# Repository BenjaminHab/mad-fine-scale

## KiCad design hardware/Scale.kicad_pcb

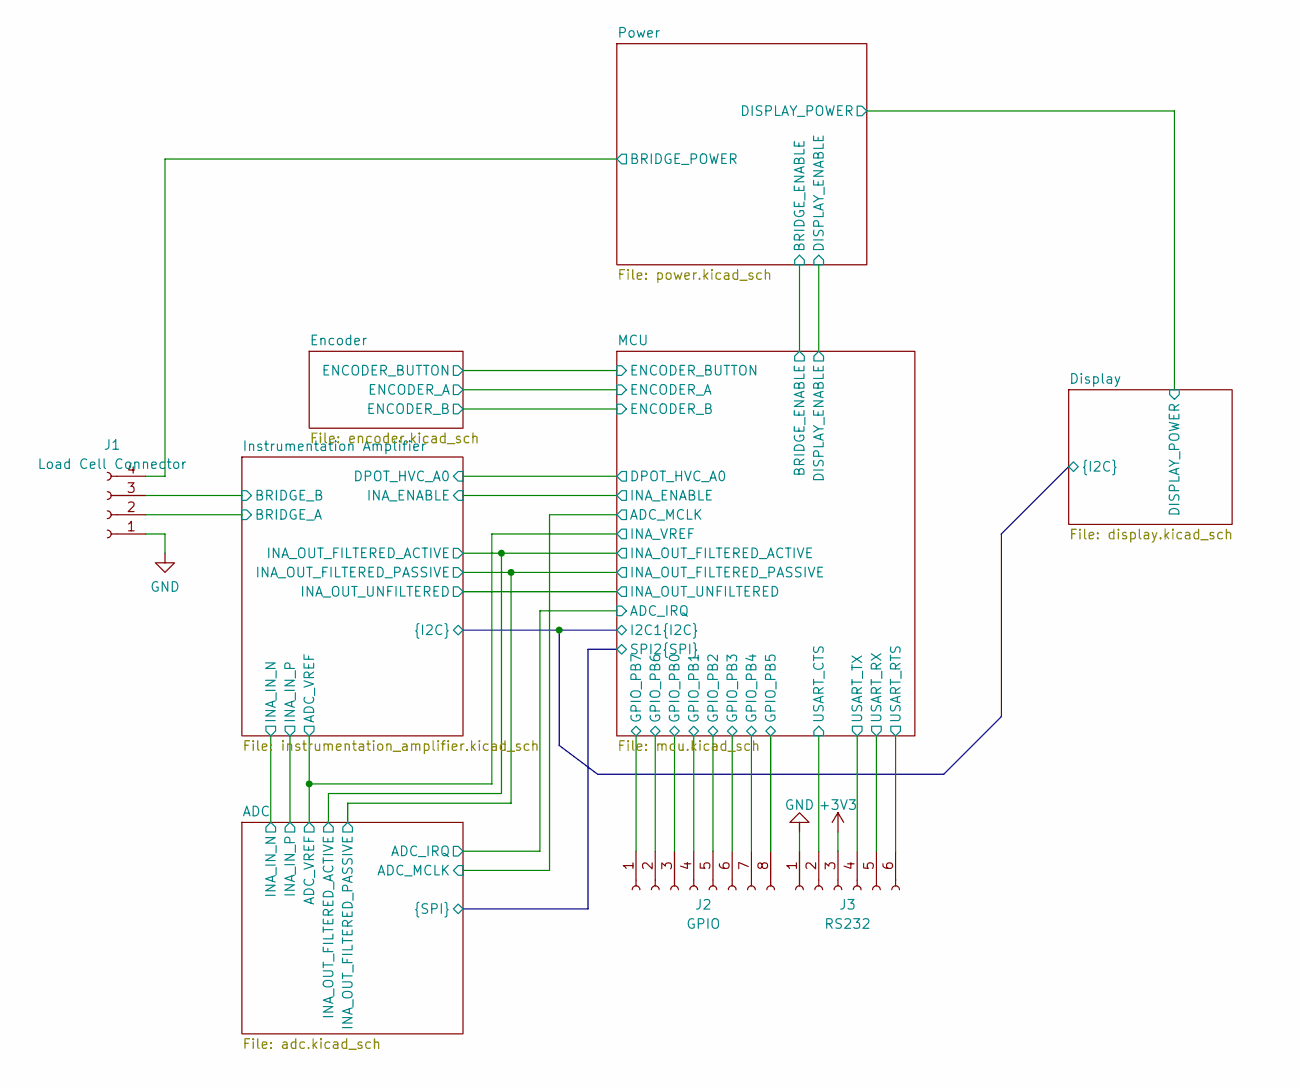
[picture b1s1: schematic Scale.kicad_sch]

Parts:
J1: Load Cell Connector; PinHeader_1x04_P2.54mm_Vertical
J2: GPIO; PinHeader_1x08_P2.54mm_Vertical
J3: RS232; PinHeader_1x06_P2.54mm_Vertical

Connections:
+3V3: J3.3; also elsewhere on the board
/Instrumentation Amplifier/BRIDGE_A: J1.2; also elsewhere on the board
/Instrumentation Amplifier/BRIDGE_B: J1.3; also elsewhere on the board
/MCU/GPIO_PB0: J2.3; also elsewhere on the board
/MCU/GPIO_PB1: J2.4; also elsewhere on the board
/MCU/GPIO_PB2: J2.5; also elsewhere on the board
/MCU/GPIO_PB3: J2.6; also elsewhere on the board
/MCU/GPIO_PB4: J2.7; also elsewhere on the board
/MCU/GPIO_PB5: J2.8; also elsewhere on the board
/MCU/GPIO_PB6: J2.2; also elsewhere on the board
/MCU/GPIO_PB7: J2.1; also elsewhere on the board
/MCU/USART_CTS: J3.2; also elsewhere on the board
/MCU/USART_RTS: J3.6; also elsewhere on the board
/MCU/USART_RX: J3.5; also elsewhere on the board
/MCU/USART_TX: J3.4; also elsewhere on the board
/Power/BRIDGE_POWER: J1.4; also elsewhere on the board
GND: J1.1, J3.1; also elsewhere on the board

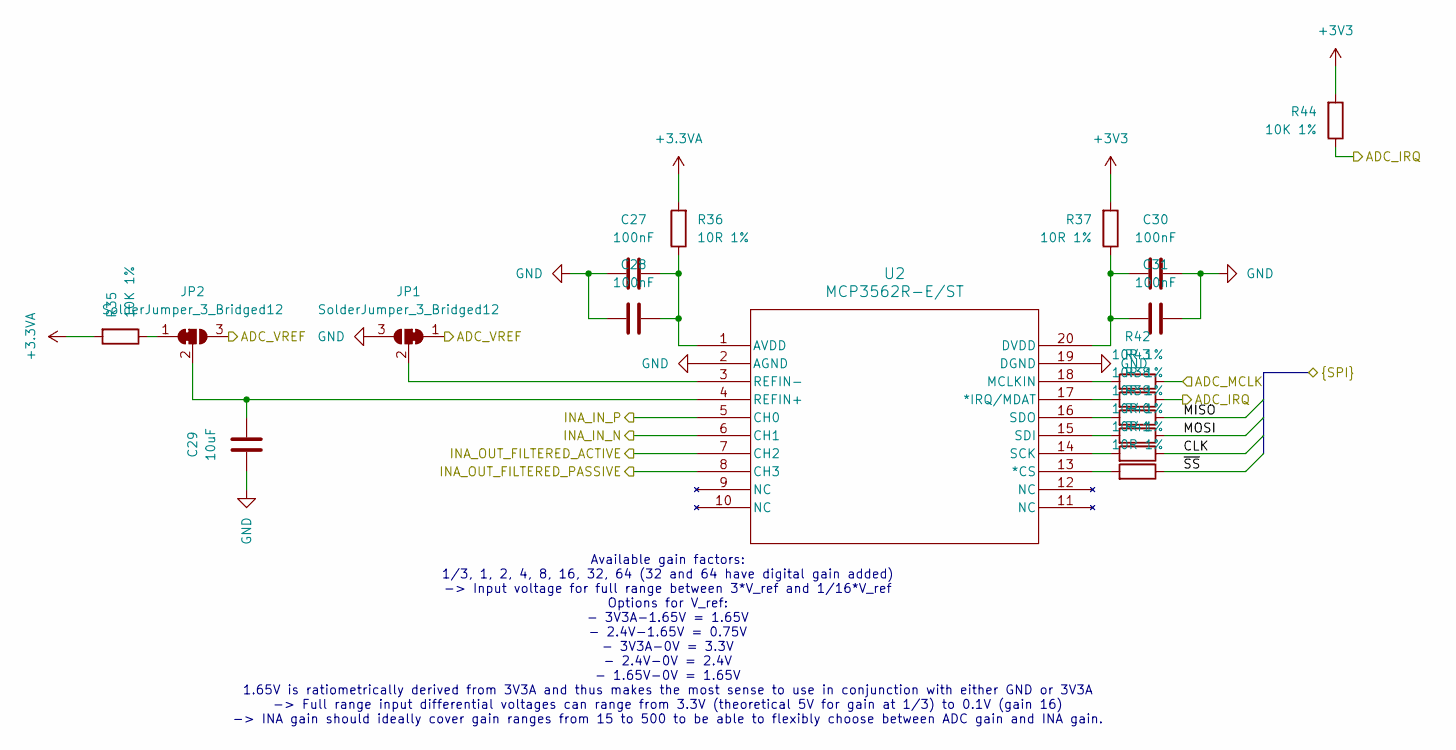
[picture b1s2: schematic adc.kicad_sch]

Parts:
C27, C28, C30, C31: 100nF; C_0603_1608Metric
C29: 10uF; C_0603_1608Metric
JP1, JP2: SolderJumper_3_Bridged12; SolderJumper-3_P1.3mm_Bridged2Bar12_RoundedPad1.0x1.5mm
R35, R44: 10K 1%; R_0603_1608Metric
R36, R37, R38, R39, R40, R41, R42, R43: 10R 1%; R_0603_1608Metric
U2: MCP3562R-E/ST; TSSOP-20_4.4x6.5mm_P0.65mm

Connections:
+3.3VA: R35.2, R36.2; also elsewhere on the board
+3V3: R37.2, R44.2; also elsewhere on the board
/ADC/ADC_IRQ: R43.1, R44.1; also elsewhere on the board
/ADC/ADC_MCLK: R42.1; also elsewhere on the board
/ADC/ADC_VREF: JP1.1 (A), JP2.3 (B); also elsewhere on the board
/ADC/CLK: R40.1; also elsewhere on the board
/ADC/INA_OUT_FILTERED_ACTIVE: U2.7 (CH2); also elsewhere on the board
/ADC/INA_OUT_FILTERED_PASSIVE: U2.8 (CH3); also elsewhere on the board
/ADC/MISO: R38.1; also elsewhere on the board
/ADC/MOSI: R39.1; also elsewhere on the board
/ADC/~SS: R41.1; also elsewhere on the board
/Instrumentation Amplifier/INA_IN_N: U2.6 (CH1); also elsewhere on the board
/Instrumentation Amplifier/INA_IN_P: U2.5 (CH0); also elsewhere on the board
GND: C27.1, C28.1, C29.1, C30.1, C31.1, JP1.3 (B), U2.2 (AGND), U2.19 (DGND); also elsewhere on the board
unnamed: JP1.2 (C), U2.3 (REFIN-)
unnamed: JP2.1 (A), R35.1
unnamed: C29.2, JP2.2 (C), U2.4 (REFIN+)
unnamed: R41.2, U2.13 (*CS)
unnamed: R43.2, U2.17 (*IRQ/MDAT)
unnamed: C27.2, C28.2, R36.1, U2.1 (AVDD)
unnamed: C30.2, C31.2, R37.1, U2.20 (DVDD)
unnamed: R42.2, U2.18 (MCLKIN)
unnamed: R40.2, U2.14 (SCK)
unnamed: R39.2, U2.15 (SDI)
unnamed: R38.2, U2.16 (SDO)

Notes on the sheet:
Available gain factors: 1/3, 1, 2, 4, 8, 16, 32, 64 (32 and 64 have digital gain added) -> Input voltage for full range between 3*V_ref and 1/16*V_ref Options for V_ref: - 3V3A-1.65V = 1.65V - 2.4V-1.65V = 0.75V - 3V3A-0V = 3.3V - 2.4V-0V = 2.4V - 1.65V-0V = 1.65V 1.65V is ratiometrically derived f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

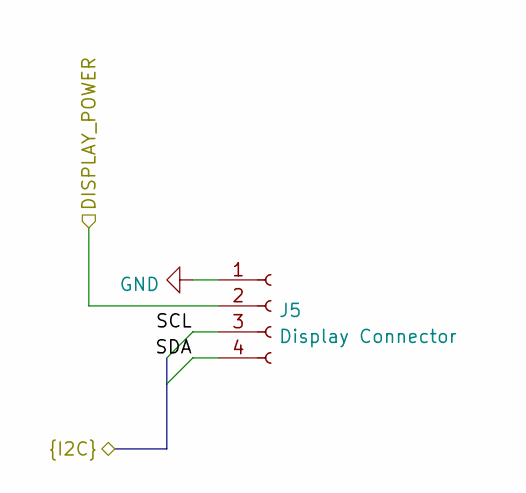
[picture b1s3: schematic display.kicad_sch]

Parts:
J5: Display Connector; PinHeader_1x04_P2.54mm_Vertical

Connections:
/Display/DISPLAY_POWER: J5.2; also elsewhere on the board
/Display/SCL: J5.3; also elsewhere on the board
/Display/SDA: J5.4; also elsewhere on the board
GND: J5.1; also elsewhere on the board

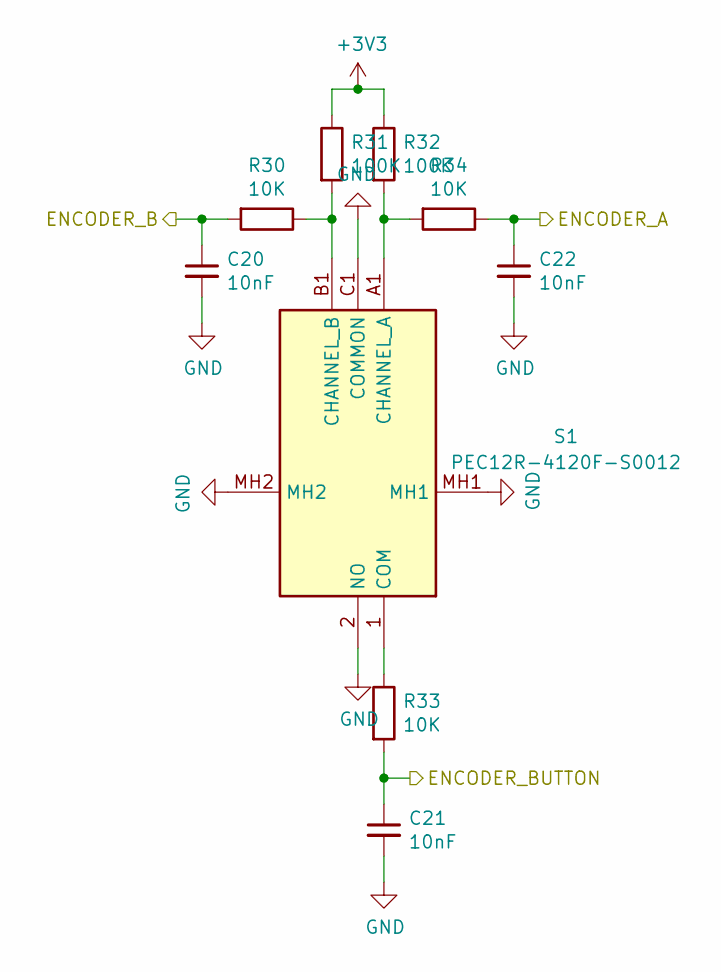
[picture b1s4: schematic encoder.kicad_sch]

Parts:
C20, C21, C22: 10nF; C_0603_1608Metric
R30, R33, R34: 10K; R_0603_1608Metric
R31, R32: 100K; R_0603_1608Metric
S1: PEC12R-4120F-S0012; PEC12R3217FS0024; Manufacturer_Part_Number PEC12R-3217F-S0024; Mouser Part Number 652-PEC12R3217FS0024

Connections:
+3V3: R31.1, R32.1; also elsewhere on the board
/Encoder/ENCODER_A: C22.1, R34.1; also elsewhere on the board
/Encoder/ENCODER_B: C20.1, R30.2; also elsewhere on the board
/Encoder/ENCODER_BUTTON: C21.1, R33.2; also elsewhere on the board
GND: C20.2, C21.2, C22.2, S1.2 (NO), S1.C1 (COMMON), S1.MH1, S1.MH2; also elsewhere on the board
unnamed: R32.2, R34.2, S1.A1 (CHANNEL_A)
unnamed: R30.1, R31.2, S1.B1 (CHANNEL_B)
unnamed: R33.1, S1.1 (COM)

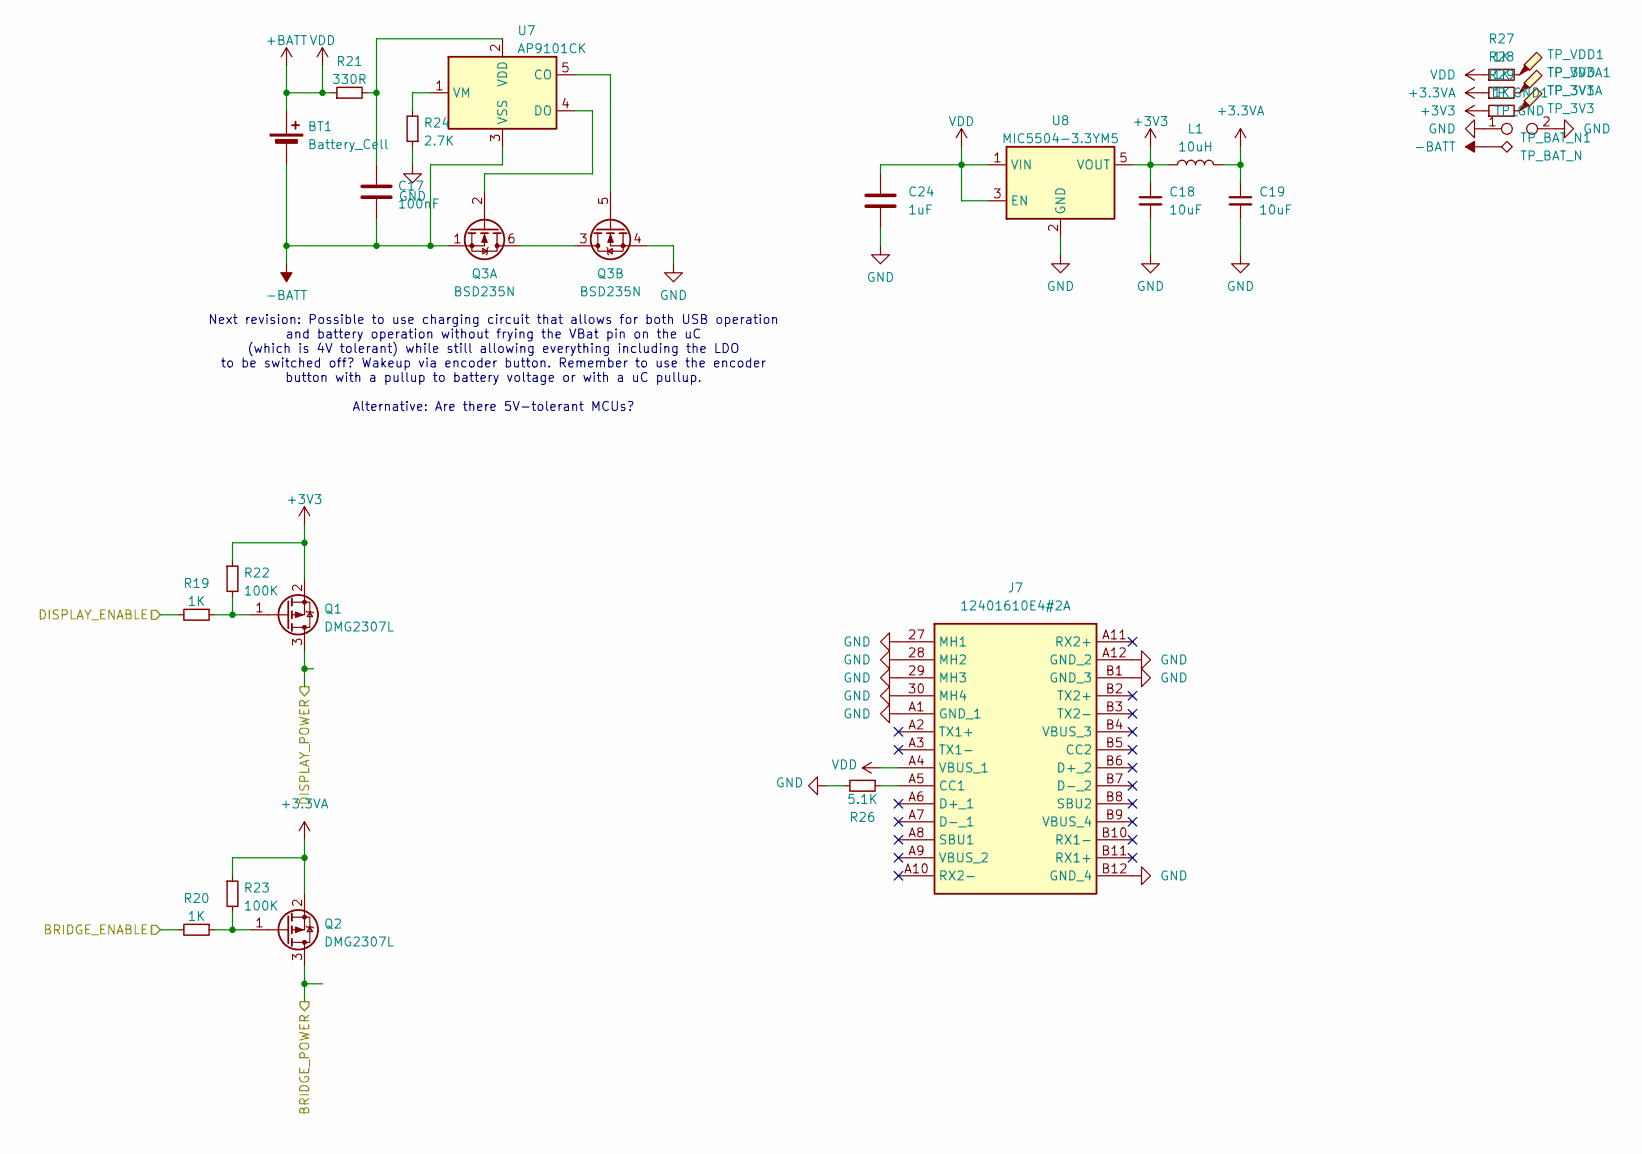
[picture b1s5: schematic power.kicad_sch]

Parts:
BT1: Battery_Cell; JST_PH_B2B-PH-K_1x02_P2.00mm_Vertical
C17: 100nF; C_0603_1608Metric
C18, C19: 10uF; C_1210_3225Metric
C24: 1uF; C_0603_1608Metric
J7: 12401610E4#2A; 12401610E42A; Manufacturer_Part_Number 12401610E4#2A
L1: 10uH; L_1210_3225Metric
Q1, Q2: DMG2307L; SOT-23
Q3: BSD235N; SOT-363_SC-70-6; MPN BSD235N
R19, R20, R27, R28, R29: 1K; R_0603_1608Metric
R21: 330R; R_0603_1608Metric
R22, R23: 100K; R_0603_1608Metric
R24: 2.7K; R_0603_1608Metric
R26: 5.1K; R_0603_1608Metric
TP_3V1: TP_3V3; TestPoint_Pad_D1.5mm
TP_3V3A1: TP_3V3A; TestPoint_Pad_D1.5mm
TP_BAT_N1: TP_BAT_N; TestPoint_Pad_D1.5mm
TP_GND1: TP_GND; R_0805_2012Metric
TP_VDD1: TP_VDD; TestPoint_Pad_D1.5mm
U7: AP9101CK; SOT-23-5; MPN AP9101CK-AHTRG1
U8: MIC5504-3.3YM5; SOT-23-5; MPN MIC5504-3.3YM5-TR

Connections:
+3.3VA: C19.1, L1.2, Q2.2 (S), R23.1, R28.1; also elsewhere on the board
+3V3: C18.1, L1.1, Q1.2 (S), R22.1, R29.1, U8.5 (VOUT); also elsewhere on the board
+BATT: BT1.1 (+), C24.2, J7.A4 (VBUS_1), R21.1, R27.1, U8.1 (VIN), U8.3 (EN)
-BATT: BT1.2 (-), C17.2, Q3.1 (S), TP_BAT_N1.1, U7.3 (VSS)
/Display/DISPLAY_POWER: Q1.3 (D); also elsewhere on the board
/MCU/BRIDGE_ENABLE: R20.2; also elsewhere on the board
/MCU/DISPLAY_ENABLE: R19.2; also elsewhere on the board
/Power/BRIDGE_POWER: Q2.3 (D); also elsewhere on the board
GND: C18.2, C19.2, C24.1, J7.27 (MH1), J7.28 (MH2), J7.29 (MH3), J7.30 (MH4), J7.A1 (GND_1), J7.A12 (GND_2), J7.B1 (GND_3), J7.B12 (GND_4), Q3.4 (S), R24.1, R26.2, TP_GND1.1, TP_GND1.2, U8.2 (GND); also elsewhere on the board
unnamed: J7.A5 (CC1), R26.1
unnamed: Q1.1 (G), R19.1, R22.2
unnamed: Q2.1 (G), R20.1, R23.2
unnamed: Q3.3 (D), Q3.6 (D)
unnamed: Q3.2 (G), U7.4 (DO)
unnamed: Q3.5 (G), U7.5 (CO)
unnamed: R27.2, TP_VDD1.1
unnamed: R28.2, TP_3V3A1.1
unnamed: R29.2, TP_3V1.1
unnamed: C17.1, R21.2, U7.2 (VDD)
unnamed: R24.2, U7.1 (VM)

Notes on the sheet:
Next revision: Possible to use charging circuit that allows for both USB operation and battery operation without frying the VBat pin on the uC (which is 4V tolerant) while still allowing everything including the LDO to be switched off? Wakeup via encoder button. Remember to use the encoder button w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

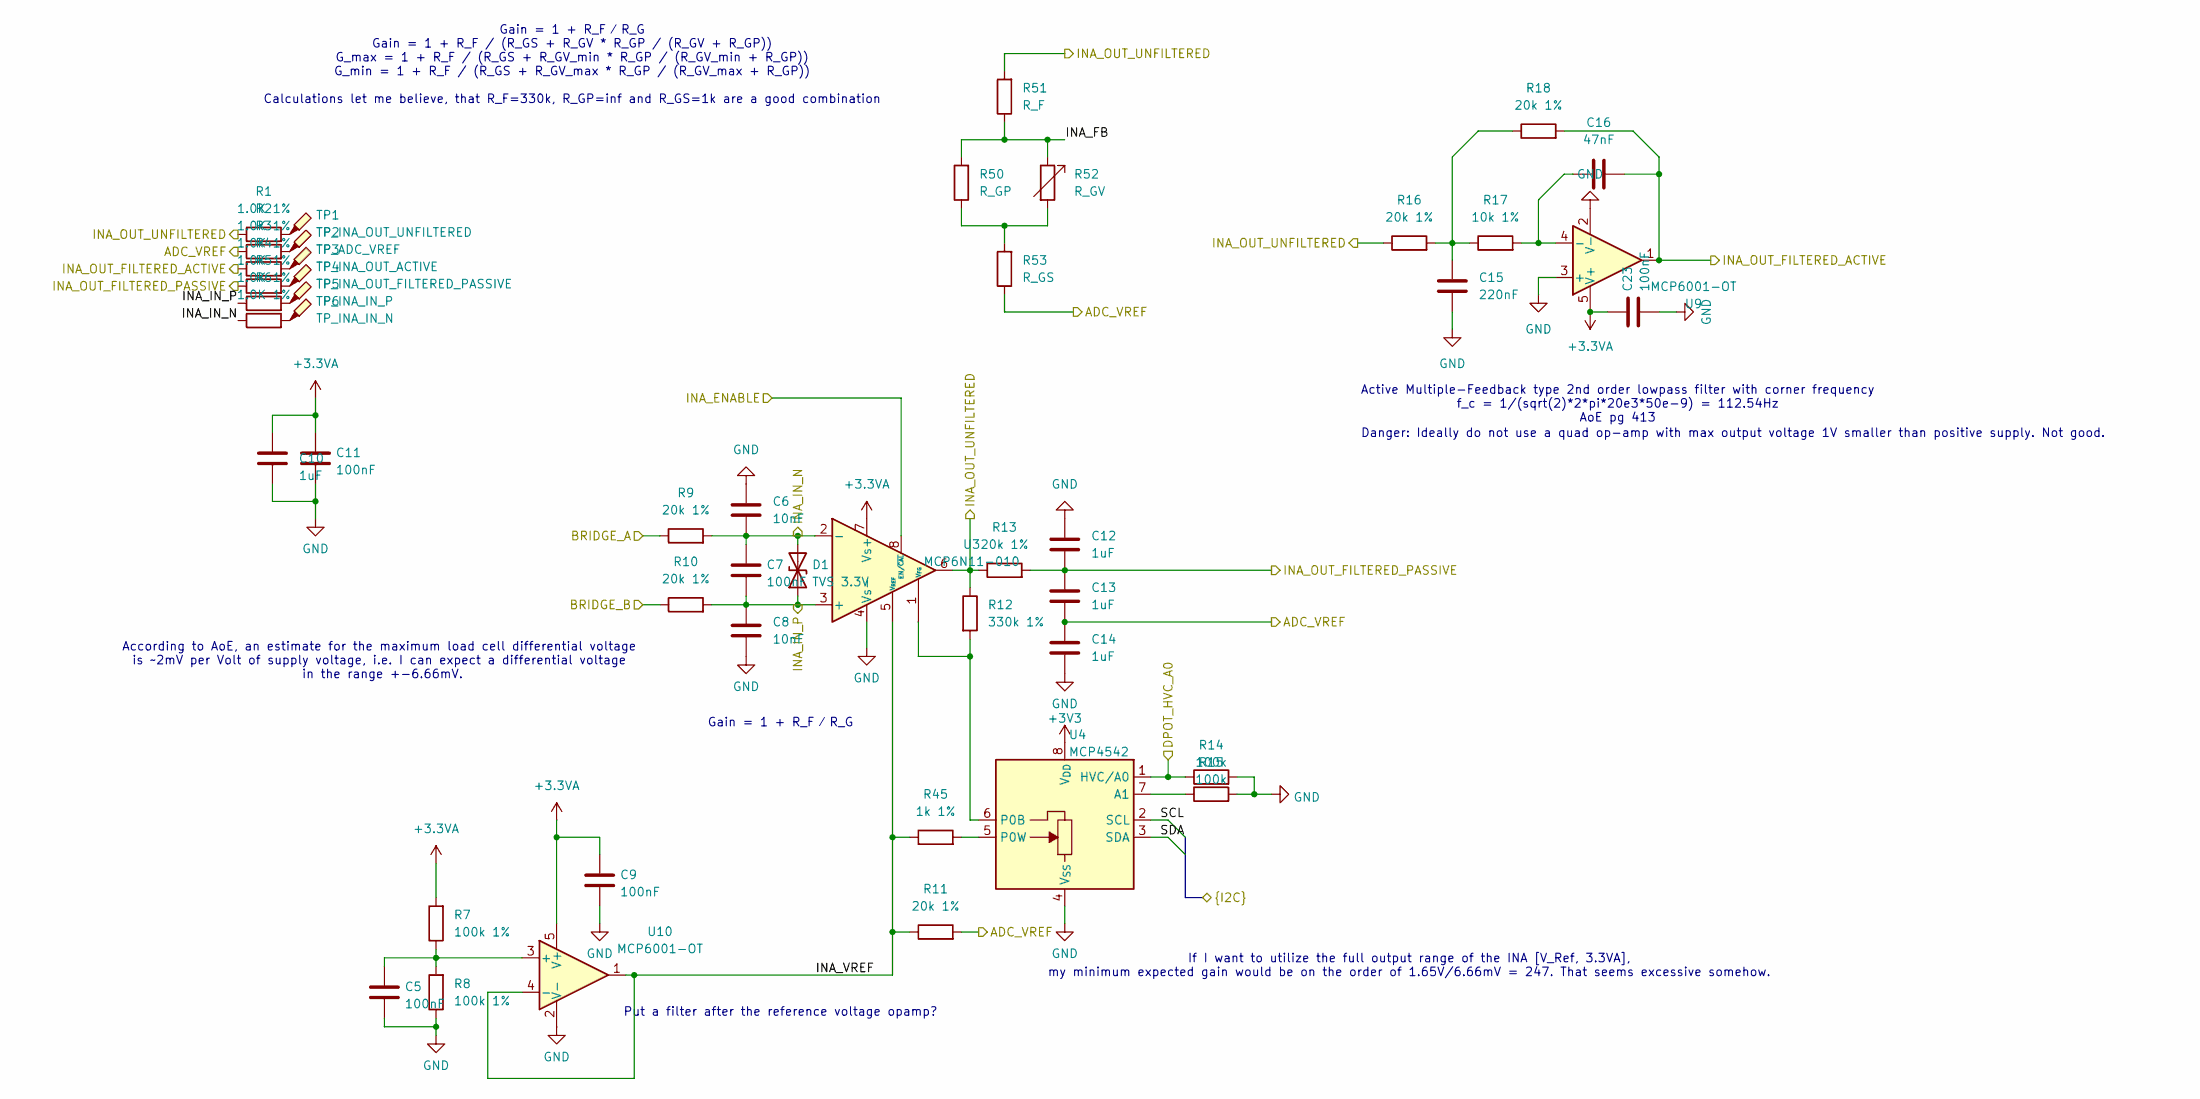
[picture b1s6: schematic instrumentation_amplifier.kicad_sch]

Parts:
C5, C7, C9, C11, C23: 100nF; C_0603_1608Metric
C6, C8: 10nF; C_0603_1608Metric
C10, C12, C13, C14: 1uF; C_0603_1608Metric
C15: 220nF; C_0603_1608Metric
C16: 47nF; C_0603_1608Metric
D1: TVS 3.3V; D_SOD-323F; MPN CDSOD323-T03
R1, R2, R3, R4, R5, R6: 1.0K 1%; R_0603_1608Metric
R7, R8: 100k 1%; R_0603_1608Metric
R9, R10, R11, R13, R16, R18: 20k 1%; R_0603_1608Metric
R12: 330k 1%; R_0603_1608Metric
R14, R15: 100k; R_0603_1608Metric
R17: 10k 1%; R_0603_1608Metric
R45: 1k 1%; R_0603_1608Metric
R50: R_GP; R_0603_1608Metric
R51: R_F; R_0603_1608Metric
R52: R_GV
R53: R_GS; R_0603_1608Metric
TP1: TP_INA_OUT_UNFILTERED; TestPoint_Pad_D1.5mm
TP2: TP_ADC_VREF; TestPoint_Pad_D1.5mm
TP3: TP_INA_OUT_ACTIVE; TestPoint_Pad_D1.5mm
TP4: TP_INA_OUT_FILTERED_PASSIVE; TestPoint_Pad_D1.5mm
TP5: TP_INA_IN_P; TestPoint_Pad_D1.5mm
TP6: TP_INA_IN_N; TestPoint_Pad_D1.5mm
U3: MCP6N11-010; SOIC-8_3.9x4.9mm_P1.27mm; MPN MCP6N11-010
U4: MCP4542; MSOP-8_3x3mm_P0.65mm; MPN MCP4542-103E/MS
U9, U10: MCP6001-OT; SOT-23-5

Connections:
+3.3VA: C9.1, C10.1, C11.1, C23.1, R7.2, U3.7 (Vs+), U9.5 (V+), U10.5 (V+); also elsewhere on the board
+3V3: U4.8 (V_{DD}); also elsewhere on the board
/ADC/ADC_VREF: C13.2, C14.1, R2.1, R11.2, R53.1; also elsewhere on the board
/ADC/INA_OUT_FILTERED_ACTIVE: C16.2, R3.1, R18.2, U9.1; also elsewhere on the board
/ADC/INA_OUT_FILTERED_PASSIVE: C12.2, C13.1, R4.1, R13.2; also elsewhere on the board
/Display/SCL: U4.2 (SCL); also elsewhere on the board
/Display/SDA: U4.3 (SDA); also elsewhere on the board
/Instrumentation Amplifier/BRIDGE_A: R9.1; also elsewhere on the board
/Instrumentation Amplifier/BRIDGE_B: R10.1; also elsewhere on the board
/Instrumentation Amplifier/DPOT_HVC_A0: R14.1, U4.1 (HVC/A0); also elsewhere on the board
/Instrumentation Amplifier/INA_ENABLE: U3.8 (EN/~CAL); also elsewhere on the board
/Instrumentation Amplifier/INA_IN_N: C6.2, C7.1, D1.2 (A2), R6.1, R9.2, U3.2 (-); also elsewhere on the board
/Instrumentation Amplifier/INA_IN_P: C7.2, C8.1, D1.1 (A1), R5.1, R10.2, U3.3 (+); also elsewhere on the board
/Instrumentation Amplifier/INA_OUT_UNFILTERED: R1.1, R12.1, R13.1, R16.1, R51.2, U3.6; also elsewhere on the board
/Instrumentation Amplifier/INA_VREF: R11.1, R45.1, U3.5 (V_{REF}), U10.1, U10.4 (-)
GND: C5.2, C6.1, C8.2, C9.2, C10.2, C11.2, C12.1, C14.2, C15.2, C23.2, R8.1, R14.2, R15.2, U3.4 (Vs-), U4.4 (V_{SS}), U9.2 (V-), U9.3 (+), U10.2 (V-); also elsewhere on the board
unnamed: C15.1, R16.2, R17.1, R18.1
unnamed: R1.2, TP1.1
unnamed: R2.2, TP2.1
unnamed: R3.2, TP3.1
unnamed: R4.2, TP4.1
unnamed: R5.2, TP5.1
unnamed: R6.2, TP6.1
unnamed: R50.1, R52.2, R53.2
unnamed: R50.2, R51.1, R52.1
unnamed: R12.2, U3.1 (V_{FG}), U4.6 (P0B)
unnamed: R15.1, U4.7 (A1)
unnamed: R45.2, U4.5 (P0W)
unnamed: C16.1, R17.2, U9.4 (-)
unnamed: C5.1, R7.1, R8.2, U10.3 (+)

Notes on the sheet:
Gain = 1 + R_F ⁄ R_G Gain = 1 + R_F / (R_GS + R_GV * R_GP / (R_GV + R_GP)) G_max = 1 + R_F / (R_GS + R_GV_min * R_GP / (R_GV_min + R_GP)) G_min = 1 + R_F / (R_GS + R_GV_max * R_GP / (R_GV_max + R_GP)) Calculations let me believe, that R_F=330k, R_GP=inf and R_GS=1k are a good combination
According to AoE, an estimate for the maximum load cell differential voltage is ~2mV per Volt of supply voltage, i.e. I can expect a differential voltage in the range +-6.66mV.
Gain = 1 + R_F ⁄ R_G
Danger: Ideally do not use a quad op-amp with max output voltage 1V smaller than positive supply. Not good.
Put a filter after the reference voltage opamp?
If I want to utilize the full output range of the INA [V_Ref, 3.3VA], my minimum expected gain would be on the order of 1.65V/6.66mV = 247. That seems excessive somehow.
Active Multiple-Feedback type 2nd order lowpass filter with corner frequency f_c = 1/(sqrt(2)*2*pi*20e3*50e-9) = 112.54Hz AoE pg 413

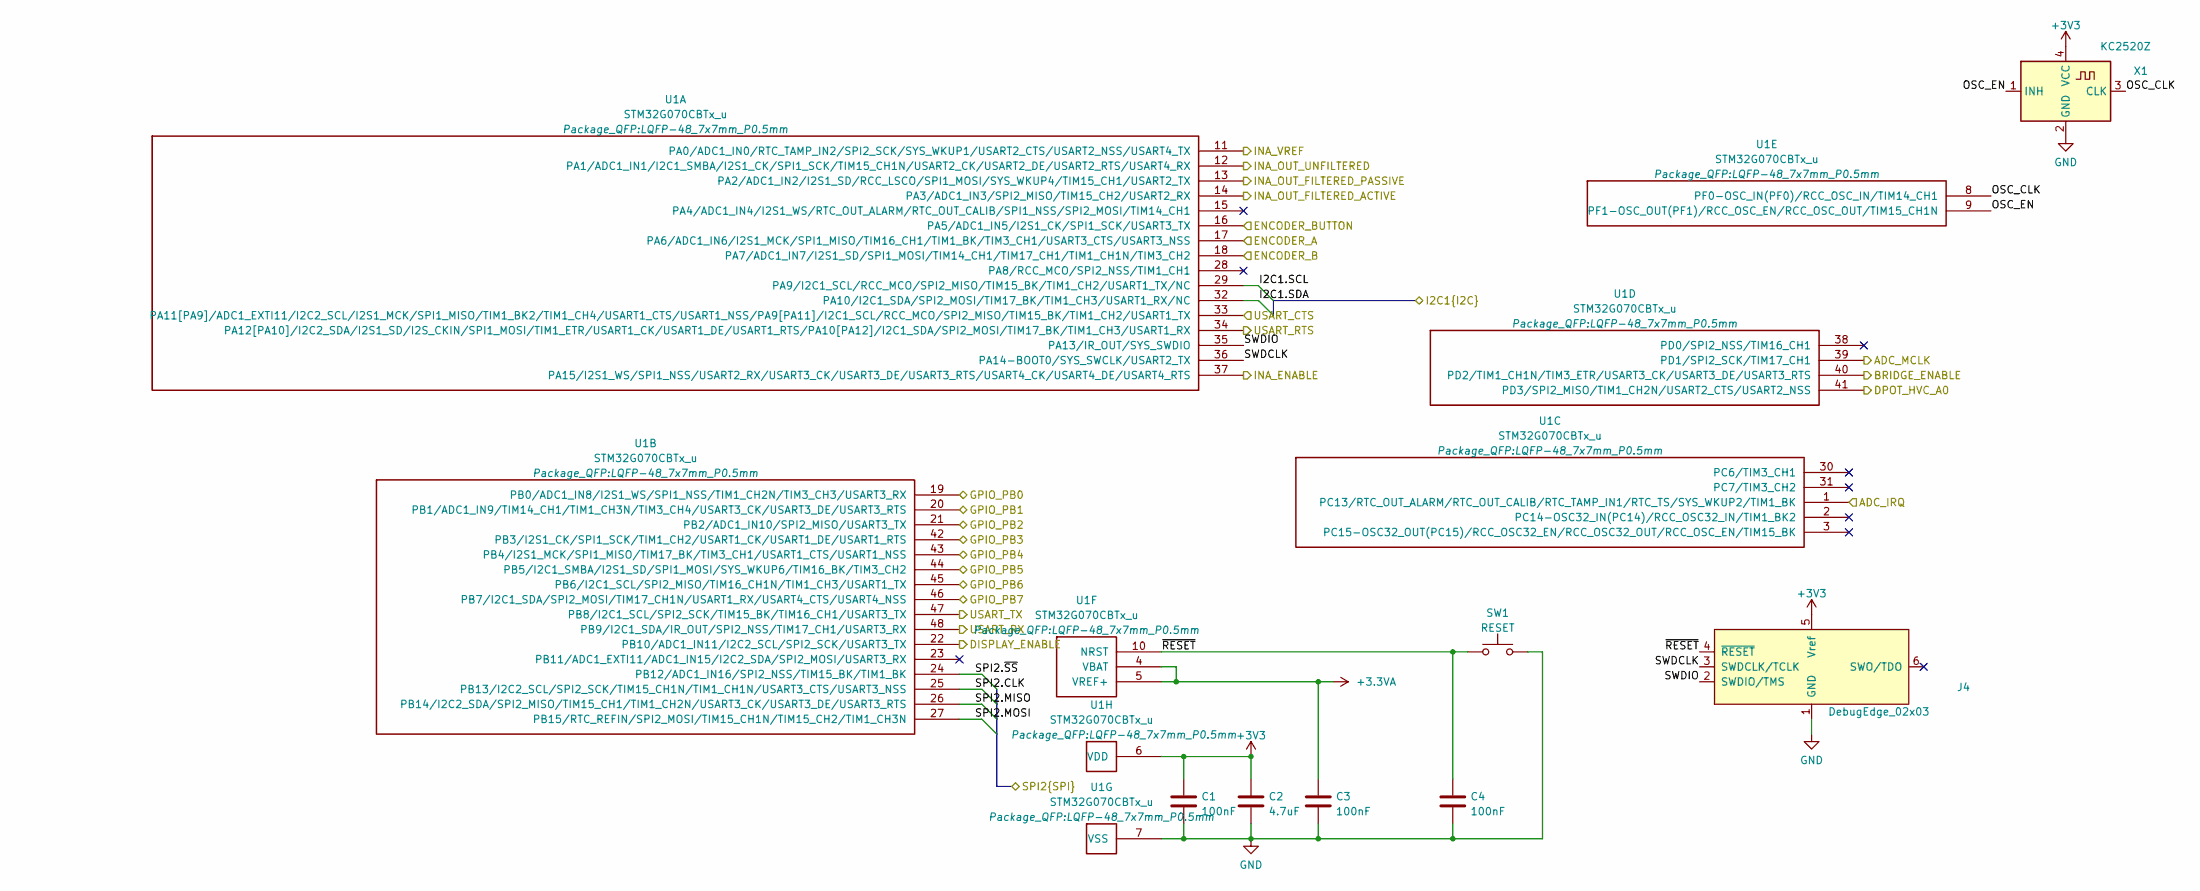
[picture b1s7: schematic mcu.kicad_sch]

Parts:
C1, C3, C4: 100nF; C_0603_1608Metric
C2: 4.7uF; C_0603_1608Metric
J4: DebugEdge_02x03; DebugEdge_2x03_Target
SW1: RESET; SW_Push_1P1T_NO_CK_KMR2
U1: STM32G070CBTx_u; LQFP-48_7x7mm_P0.5mm
X1: KC2520Z; Oscillator_SMD_Kyocera_KC2520Z-4Pin_2.5x2.0mm; MPN KC2520Z48.0000C1KX00

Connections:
+3.3VA: C3.1, U1.4 (VBAT), U1.5 (VREF+); also elsewhere on the board
+3V3: C1.1, C2.1, J4.5 (Vref), U1.6 (VDD), X1.4 (VCC); also elsewhere on the board
/ADC/ADC_IRQ: U1.1 (PC13/RTC_OUT_ALARM/RTC_OUT_CALIB/RTC_TA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); also elsewhere on the board
/ADC/ADC_MCLK: U1.39 (PD1/SPI2_SCK/TIM17_CH1); also elsewhere on the board
/ADC/ADC_VREF: U1.11 (PA0/ADC1_IN0/RTC_TAMP_IN2/SPI2_SCK/SYS_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); also elsewhere on the board
/ADC/CLK: U1.25 (PB13/I2C2_SCL/SPI2_SCK/TIM15_CH1N/TIM1_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); also elsewhere on the board
/ADC/INA_OUT_FILTERED_ACTIVE: U1.14 (PA3/ADC1_IN3/SPI2_MISO/TIM15_CH2/USART2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); also elsewhere on the board
/ADC/INA_OUT_FILTERED_PASSIVE: U1.13 (PA2/ADC1_IN2/I2S1_SD/RCC_LSCO/SPI1_MOSI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); also elsewhere on the board
/ADC/MISO: U1.26 (PB14/I2C2_SDA/SPI2_MISO/TIM15_CH1/TIM1_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); also elsewhere on the board
/ADC/MOSI: U1.27 (PB15/RTC_REFIN/SPI2_MOSI/TIM15_CH1N/TIM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); also elsewhere on the board
/ADC/~SS: U1.24 (PB12/ADC1_IN16/SPI2_NSS/TIM15_BK/TIM1_BK); also elsewhere on the board
/Display/SCL: U1.29 (PA9/I2C1_SCL/RCC_MCO/SPI2_MISO/TIM15_BK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); also elsewhere on the board
/Display/SDA: U1.32 (PA10/I2C1_SDA/SPI2_MOSI/TIM17_BK/TIM1_C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); also elsewhere on the board
/Encoder/ENCODER_A: U1.17 (PA6/ADC1_IN6/I2S1_MCK/SPI1_MISO/TIM16_C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); also elsewhere on the board
/Encoder/ENCODER_B: U1.18 (PA7/ADC1_IN7/I2S1_SD/SPI1_MOSI/TIM14_CH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); also elsewhere on the board
/Encoder/ENCODER_BUTTON: U1.16 (PA5/ADC1_IN5/I2S1_CK/SPI1_SCK/USART3_TX); also elsewhere on the board
/Instrumentation Amplifier/DPOT_HVC_A0: U1.41 (PD3/SPI2_MISO/TIM1_CH2N/USART2_CTS/USAR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); also elsewhere on the board
/Instrumentation Amplifier/INA_ENABLE: U1.37 (PA15/I2S1_WS/SPI1_NSS/USART2_RX/USART3_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); also elsewhere on the board
/Instrumentation Amplifier/INA_OUT_UNFILTERED: U1.12 (PA1/ADC1_IN1/I2C1_SMBA/I2S1_CK/SPI1_SCK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); also elsewhere on the board
/MCU/BRIDGE_ENABLE: U1.40 (PD2/TIM1_CH1N/TIM3_ETR/USART3_CK/USART3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); also elsewhere on the board
/MCU/DISPLAY_ENABLE: U1.22 (PB10/ADC1_IN11/I2C2_SCL/SPI2_SCK/USART3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); also elsewhere on the board
/MCU/GPIO_PB0: U1.19 (PB0/ADC1_IN8/I2S1_WS/SPI1_NSS/TIM1_CH2N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); also elsewhere on the board
/MCU/GPIO_PB1: U1.20 (PB1/ADC1_IN9/TIM14_CH1/TIM1_CH3N/TIM3_C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); also elsewhere on the board
/MCU/GPIO_PB2: U1.21 (PB2/ADC1_IN10/SPI2_MISO/USART3_TX); also elsewhere on the board
/MCU/GPIO_PB3: U1.42 (PB3/I2S1_CK/SPI1_SCK/TIM1_CH2/USART1_CK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); also elsewhere on the board
/MCU/GPIO_PB4: U1.43 (PB4/I2S1_MCK/SPI1_MISO/TIM17_BK/TIM3_CH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); also elsewhere on the board
/MCU/GPIO_PB5: U1.44 (PB5/I2C1_SMBA/I2S1_SD/SPI1_MOSI/SYS_WKU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); also elsewhere on the board
/MCU/GPIO_PB6: U1.45 (PB6/I2C1_SCL/SPI2_MISO/TIM16_CH1N/TIM1_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); also elsewhere on the board
/MCU/GPIO_PB7: U1.46 (PB7/I2C1_SDA/SPI2_MOSI/TIM17_CH1N/USART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); also elsewhere on the board
/MCU/OSC_CLK: U1.8 (PF0-OSC_IN(PF0)/RCC_OSC_IN/TIM14_CH1), X1.3 (CLK)
/MCU/OSC_EN: U1.9 (PF1-OSC_OUT(PF1)/RCC_OSC_EN/RCC_OSC_OUT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), X1.1 (INH)
/MCU/SWDCLK: J4.3 (SWDCLK/TCLK), U1.36 (PA14-BOOT0/SYS_SWCLK/USART2_TX)
/MCU/SWDIO: J4.2 (SWDIO/TMS), U1.35 (PA13/IR_OUT/SYS_SWDIO)
/MCU/USART_CTS: U1.33 (PA11[PA9]/ADC1_EXTI11/I2C2_SCL/I2S1_MCK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); also elsewhere on the board
/MCU/USART_RTS: U1.34 (PA12[PA10]/I2C2_SDA/I2S1_SD/I2S_CKIN/SP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); also elsewhere on the board
/MCU/USART_RX: U1.48 (PB9/I2C1_SDA/IR_OUT/SPI2_NSS/TIM17_CH1/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); also elsewhere on the board
/MCU/USART_TX: U1.47 (PB8/I2C1_SCL/SPI2_SCK/TIM15_BK/TIM16_CH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); also elsewhere on the board
/MCU/~RESET: C4.1, J4.4 (~RESET), SW1.1, U1.10 (NRST)
GND: C1.2, C2.2, C3.2, C4.2, J4.1 (GND), SW1.2, U1.7 (VSS), X1.2 (GND); also elsewhere on the board

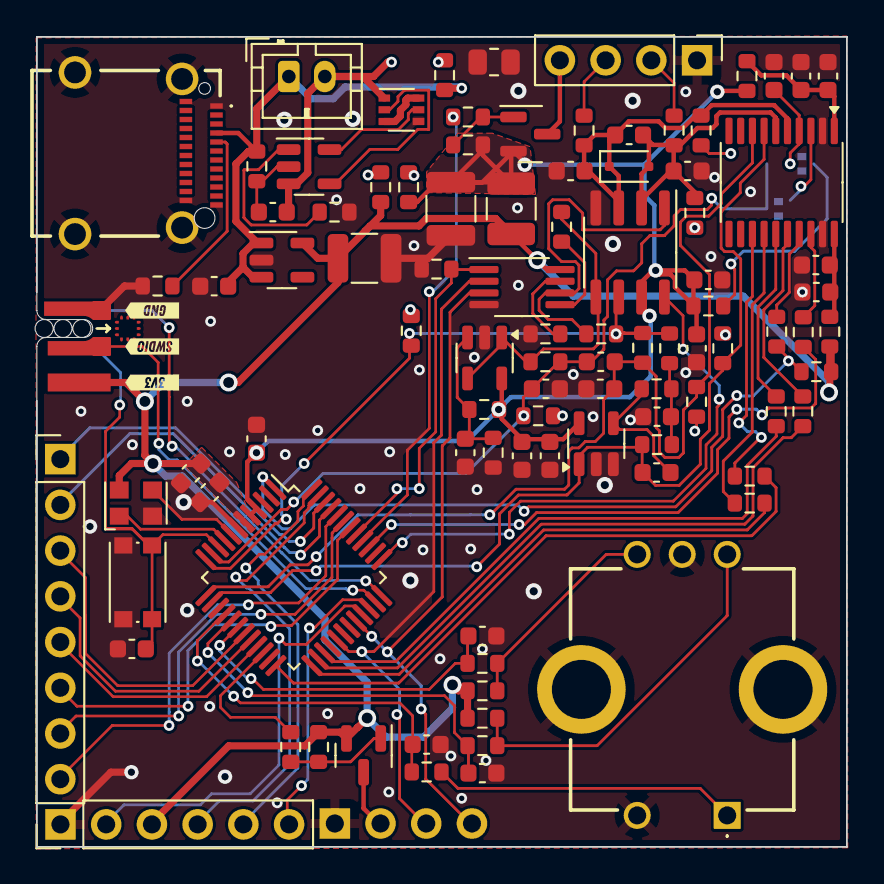
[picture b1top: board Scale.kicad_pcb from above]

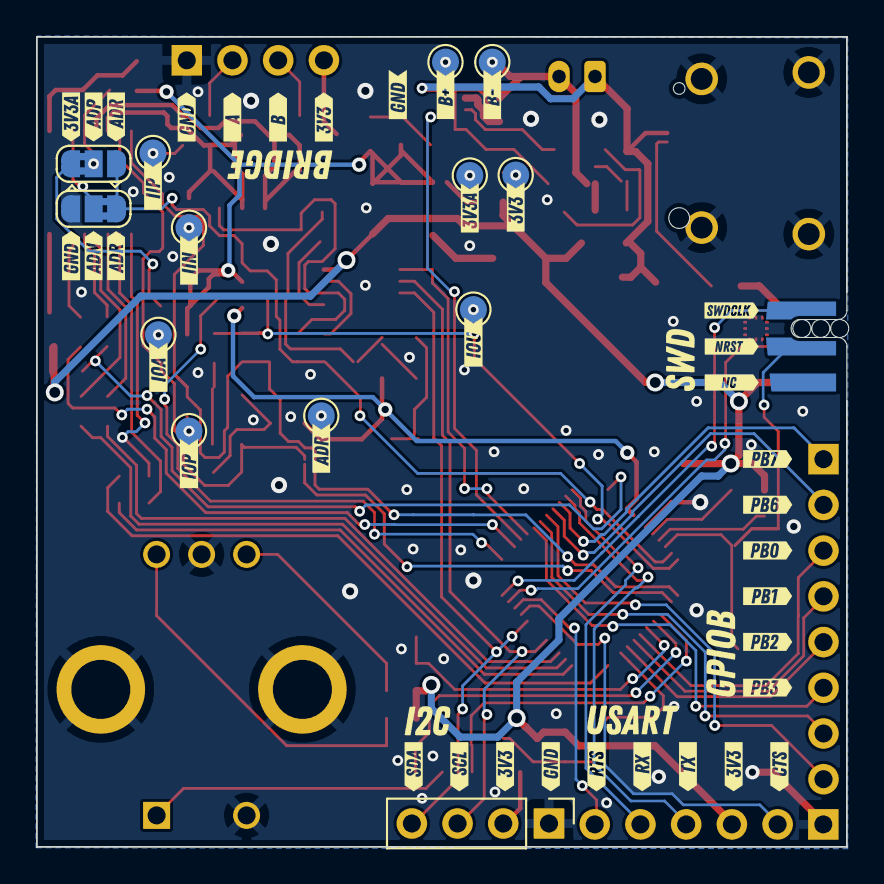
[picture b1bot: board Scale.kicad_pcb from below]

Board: 2 copper layers, 45.0 x 45.0 mm, 158 parts (59 on the bottom side), 85 nets.

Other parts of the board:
kibuzzard-69235A0F: G***; kibuzzard-69235A0F
kibuzzard-69235A05: G***; kibuzzard-69235A05
kibuzzard-69235A65: G***; kibuzzard-69235A65
kibuzzard-69235A78: G***; kibuzzard-69235A78
kibuzzard-69235A81: G***; kibuzzard-69235A81
kibuzzard-69235C2C: G***; kibuzzard-69235C2C
kibuzzard-69235C3D: G***; kibuzzard-69235C3D
kibuzzard-69235C19: G***; kibuzzard-69235C19
kibuzzard-69235C25: G***; kibuzzard-69235C25
kibuzzard-69235C31: G***; kibuzzard-69235C31
kibuzzard-69235C43: G***; kibuzzard-69235C43
kibuzzard-69235C86: G***; kibuzzard-69235C86
kibuzzard-69235CAB: G***; kibuzzard-69235CAB
kibuzzard-69235CD0: G***; kibuzzard-69235CD0
kibuzzard-69235CE7: G***; kibuzzard-69235CE7
kibuzzard-69235D1A: G***; kibuzzard-69235D1A
kibuzzard-69235D2C: G***; kibuzzard-69235D2C
kibuzzard-69235D7B: G***; kibuzzard-69235D7B
kibuzzard-69235D46: G***; kibuzzard-69235D46
kibuzzard-69235D61: G***; kibuzzard-69235D61
kibuzzard-69235D70: G***; kibuzzard-69235D70
kibuzzard-69235D86: G***; kibuzzard-69235D86
kibuzzard-69235DBF: G***; kibuzzard-69235DBF
kibuzzard-69235DD0: G***; kibuzzard-69235DD0
kibuzzard-69235DDD: G***; kibuzzard-69235DDD
kibuzzard-69235DE8: G***; kibuzzard-69235DE8
kibuzzard-69235E1A: G***; kibuzzard-69235E1A
kibuzzard-69235E07: G***; kibuzzard-69235E07
kibuzzard-69235E34: G***; kibuzzard-69235E34
kibuzzard-69235E43: G***; kibuzzard-69235E43
kibuzzard-69235E53: G***; kibuzzard-69235E53
kibuzzard-69235E66: G***; kibuzzard-69235E66
kibuzzard-69235E74: G***; kibuzzard-69235E74
kibuzzard-69235E84: G***; kibuzzard-69235E84
kibuzzard-69235EA0: G***; kibuzzard-69235EA0
kibuzzard-69235EC4: G***; kibuzzard-69235EC4
kibuzzard-69235ED0: G***; kibuzzard-69235ED0
kibuzzard-69235EDC: G***; kibuzzard-69235EDC
kibuzzard-69235EE8: G***; kibuzzard-69235EE8
kibuzzard-69235EF4: G***; kibuzzard-69235EF4
kibuzzard-69235F49: G***; kibuzzard-69235F49
kibuzzard-69235FA0: G***; kibuzzard-69235FA0
kibuzzard-69235FE1: G***; kibuzzard-69235FE1
kibuzzard-692359F1: G***; kibuzzard-692359F1
kibuzzard-692360F1: G***; kibuzzard-692360F1
kibuzzard-69236006: G***; kibuzzard-69236006
kibuzzard-69236027: G***; kibuzzard-69236027
kibuzzard-69236067: G***; kibuzzard-69236067
kibuzzard-69236118: G***; kibuzzard-69236118

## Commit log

2022-06-05 Initial commit courtesy of CubeMX and mad-lightning-stick
2022-06-05 Fixed Display: At fault was the output speed of the i2c pins
2024-02-26 Started Rust subproject
2024-03-01 added gitignore
2024-03-01 Removed build files from index, first experiments with rust
2025-07-11 Added datasheets for INA and rheo
2025-07-11 Add todos and try to talk to rheo on i2c
2025-07-14 Set up debugging with vscode
2025-07-14 Fix compiler warning about unused results
2025-07-14 Fixed vscode launch config
2025-07-14 Get I2C with rheo working
2025-08-10 Added inspiration from Microchip reference design to todo list
2025-08-10 Added justification for reference voltage
2025-08-12 Refined todo list for hardware revision
2025-08-12 Reorganised and added datasheets, application notes etc
2025-08-12 Updated schematic according to reference design
2025-08-13 Remove backups and lock files
2025-11-03 Include active filter, ext. ADC, changes to power supply
2025-11-03 Added correct symbol and libraries for ADC
2025-11-12 Regenerated reference designators, changed to rail-to-rail op-amps
2025-11-17 Add KiCad-specific .gitignore
2025-11-17 Add ADC datasheet and reference design
2025-11-17 Major changes to schematic
2025-11-17 Started on pcb
2025-11-17 Add rust-specific .gitignore
2025-11-17 Remove csv from .gitignore
2025-11-17 Cleanup hardware folder
2025-11-17 Added gain calculations Pluto notebook
2025-11-17 Added solder bridges and calculated resistor values for INA
2025-11-17 Set jumper footprints and updated design rules for Oshpark After Dark
2025-11-18 Added battery protection IC datasheet
2025-11-18 Realized that 5V to VBat pin would fry the uC and abandoned ultra-low power design. Deferred to next revision.
    A
    A
    A
    A
    A
    A
2025-11-18 Some more routing
2025-11-21 Ran electrical check on schematic and implemented corrections
2025-11-21 Updated design rules and ran and implemented DRC
2025-11-23 Added labels
2025-11-23 Rearrange labels
2025-11-27 Added test point
2025-11-27 Moved schematic and footprint to common library
2025-11-27 Removed old silkscreen design files
2025-11-27 Move vias to fix silkscreen
2025-11-27 Fixed encoder and usb 3D models
2025-11-27 Fix Silkscreen
2025-11-27 Embed fonts
2025-11-27 Move board edge for manufacturing
2025-12-02 Added net classes
2025-12-04 Embassy starting point: ADC example
2025-12-04 Can build embassy adc example
2025-12-04 Can flash and attach with cargo embed
2025-12-04 Added Pluto Notebook for ADC data analysis
2025-12-04 Moved rheo functionality into module and tested it
2025-12-04 Fixed logging issues for cargo embed
2025-12-04 Add HSE config. Blink LED. Logging still borked.
2025-12-04 Update gitignore
2025-12-04 Fixed gain calculation
2025-12-04 Used example to get mutual exclusive use of I2C working
2025-12-04 Analyse ADC measurement problem
2025-12-04 Added svd file for debugging
2025-12-04 Try to move towards sharing the I2C peripheral; currently borked
2025-12-04 Rheo communication established
2025-12-04 Reorganized source files to make building different binaries an option
2025-12-04 Config for debugging
2025-12-04 Cleanup of old hardware files
2025-12-04 Move to notion board
2025-12-04 Updated ibom
2025-12-04 Add peripheral tests
2025-12-04 Modify vscode debug config to allow debugging currently open rust file
2025-12-04 Started work on display integration
2025-12-04 Fixed vscode tasks and launch for debugging active file
2026-01-31 Added note because of resistor availability
2026-01-31 Began troubleshooting of display connection
2026-02-05 Updated pins to reflect hardware changes
2026-02-05 Added adc test
2026-02-05 Added MCP3562R functionality in code, preliminary test positive
